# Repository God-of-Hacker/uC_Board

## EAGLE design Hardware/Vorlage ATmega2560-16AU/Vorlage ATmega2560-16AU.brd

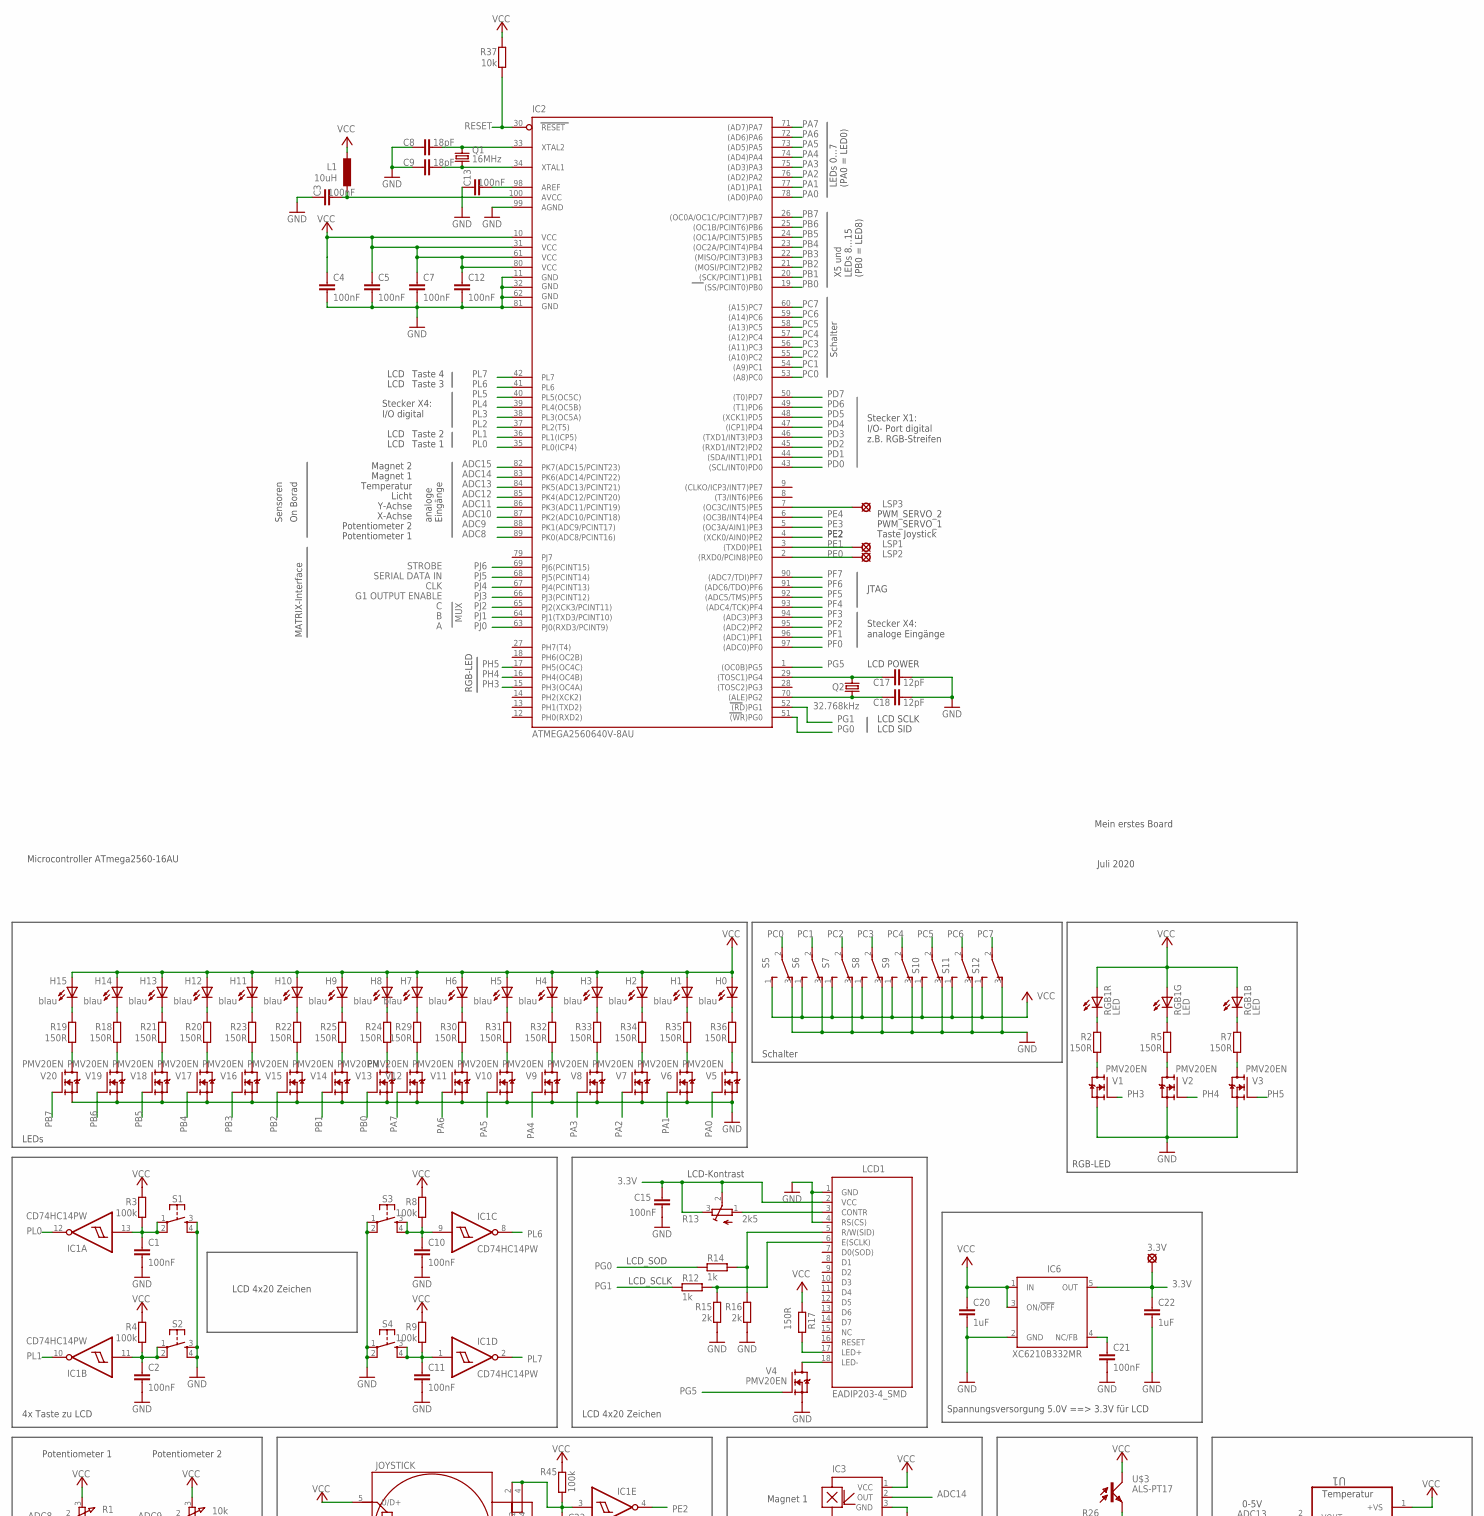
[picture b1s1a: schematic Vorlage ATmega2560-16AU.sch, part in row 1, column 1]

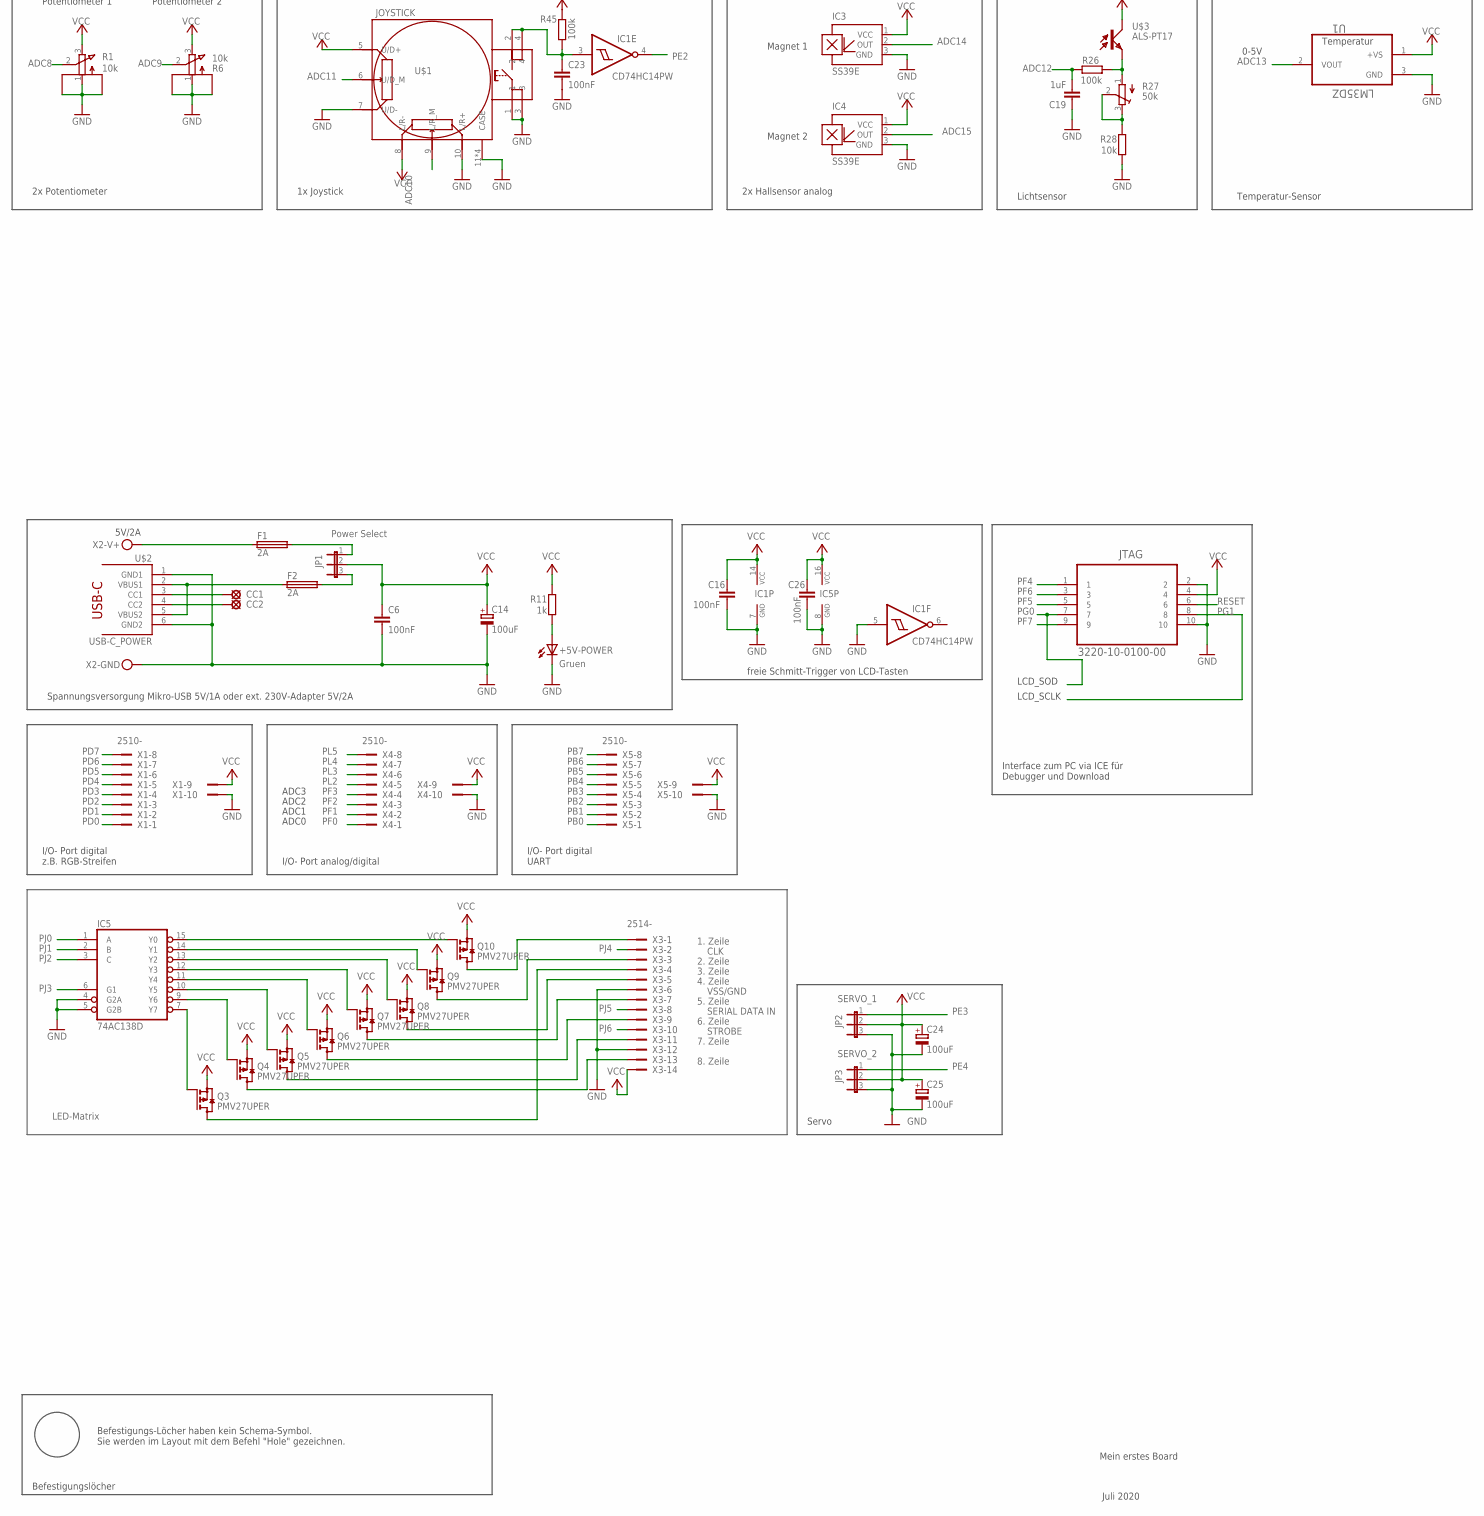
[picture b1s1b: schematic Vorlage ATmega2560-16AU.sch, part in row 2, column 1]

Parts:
3.3V: 3.3V; LSP11
+5V-POWER: Gruen; CHIPLED_1206
C1, C2, C3, C4, C5, C7, C10, C11, C12, C13, C21, C23: 100nF; C0805
C6, C15, C16, C26: 100nF; C1206
C8, C9: 18pF; C0805K
C14, C24, C25: 100uF; UD-6,3X5,8_NICHICON
C17, C18: 12pF; C0805K
C19, C20, C22: 1uF; C0805
CC1, CC2: LSP11
F1, F2: 2A; F1206
H0, H1, H2, H3, H4, H5, H6, H7, H8, H9, H10, H11, H12, H13, H14, H15: blau; CHIPLED_1206
IC1: CD74HC14PW; SO14
IC2: ATMEGA2560640V-8AU; TQFP100
IC3, IC4: SS39E; SOT23-W
IC5: 74AC138D; SO16
IC6: XC6210B332MR; SOT23-DBV
JP1: Power Select; JP2
JP2: SERVO_1; JP2
JP3: SERVO_2; JP2
JTAG: 3220-10-0100-00; SAMTEC_FTS-105-01-L-D
L1: 10uH; L2825P
LCD1: EADIP203-4_SMD; EADIP203-4SMD
LSP1, LSP2, LSP3: LSP11
Q1: 16MHz; HC49UP
Q2: 32.768kHz; TC38H
Q3, Q4, Q5, Q6, Q7, Q8, Q9, Q10: PMV27UPER; SOT23
R1, R6: 10k; EVUF
R2, R5, R7, R18, R19, R20, R21, R22, R23, R24, R25, R29, R30, R31, R32, R33, R34, R35, R36: 150R; R0805
R3, R4, R8, R9, R26, R45: 100k; R0805
R11, R12, R14: 1k; R0805
R13: 2k5; 3223G
R15, R16: 2k; R0805
R17: 150R; R1206
R27: 50k; 3223G
R28, R37: 10k; R0805
RGB1: LED; LED_MIT_DIFUSOR
S1, S2, S3, S4: TS42_4PAD
S5, S6, S7, S8, S9, S10, S11, S12: TL36POSPDT_5MM; SPDT_5MM
U1: LM35DZ; TO127P254X495-3P
U$1: JOYSTICK; RKJXV1224005
U$2: USB-C_POWER; USB-C
U$3: ALS-PT17; SOD232-W
V1, V2, V3, V4, V5, V6, V7, V8, V9, V10, V11, V12, V13, V14, V15, V16, V17, V18, V19, V20: PMV20EN; SOT23
X1, X4, X5: 2510-; PAK100/2500-10
X2: +5V; MKDSN1,5/2-5,08
X3: 2514-; PAK100/2500-14

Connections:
3.3V: 3.3V.MP, C15.1, C22.1, IC6.5 (OUT), LCD1.2 (VCC), R13.2 (S), R13.3 (E)
ADC8: IC2.89 (PK0(ADC8/PCINT16)), R1.2 (S)
ADC9: IC2.88 (PK1(ADC9/PCINT17)), R6.2 (S)
ADC10: IC2.87 (PK2(ADC10/PCINT18)), U$1.9 (L/R_M)
ADC11: IC2.86 (PK3(ADC11/PCINT19)), U$1.6 (U/D_M)
ADC12: C19.2, IC2.85 (PK4(ADC12/PCINT20)), R26.2
ADC13: IC2.84 (PK5(ADC13/PCINT21)), U1.2 (VOUT)
ADC14: IC2.83 (PK6(ADC14/PCINT22)), IC3.2 (OUT)
ADC15: IC2.82 (PK7(ADC15/PCINT23)), IC4.2 (OUT)
GND: +5V-POWER.C, C1.2, C2.2, C3.1, C4.2, C5.2, C6.2, C7.2, C8.1, C9.2, C10.2, C11.2, C12.2, C13.1, C14.-, C15.2, C16.2, C17.2, C18.2, C19.1, C20.2, C21.2, C22.2, C23.2, C24.-, C25.-, C26.2, IC1.5 (I), IC1.7 (GND), IC2.11 (GND), IC2.32 (GND1), IC2.62 (GND2), IC2.81 (GND3), IC2.99 (AGND), IC3.3 (GND), IC4.3 (GND), IC5.4 (G2A), IC5.5 (G2B), IC5.8 (GND), IC6.2 (GND), JP2.3, JP3.3, JTAG.2, JTAG.10, LCD1.1 (GND), LCD1.4 (RS(CS)), R1.1 (A), R1.M1, R1.M2, R6.1 (A), R6.M1, R6.M2, R15.1, R16.1, R28.1, S1.3, S1.4, S2.3, S2.4, S3.1, S3.2, S4.1, S4.2, S5.3 (O), S6.3 (O), S7.3 (O), S8.3 (O), S9.3 (O), S10.3 (O), S11.3 (O), S12.3 (O), U1.3 (GND), U$1.1, U$1.3, U$1.7 (U/D-), U$1.10 (L/R+), U$1.11 (CASE), U$1.12 (CASE), U$1.15 (CASE), U$1.16 (CASE), U$2.1 (GND1), U$2.6 (GND2), V1.2 (S), V2.2 (S), V3.2 (S), V4.2 (S), V5.2 (S), V6.2 (S), V7.2 (S), V8.2 (S), V9.2 (S), V10.2 (S), V11.2 (S), V12.2 (S), V13.2 (S), V14.2 (S), V15.2 (S), V16.2 (S), V17.2 (S), V18.2 (S), V19.2 (S), V20.2 (S), X1.10, X2.1.1, X2.1.2, X3.6, X3.12, X4.10, X5.10
H1: H15.C, R19.2
H7: H7.C, R29.2
unnamed: R7.2, RGB1.1 (C)
unnamed: R5.2, RGB1.2 (C)
unnamed: F1.2, JP1.1
unnamed: F2.2, JP1.3
unnamed: R36.1, V5.3 (D)
unnamed: R35.1, V6.3 (D)
unnamed: R34.1, V7.3 (D)
unnamed: CC1.MP, U$2.3 (CC1)
unnamed: C23.1, IC1.3 (I), R45.2, U$1.2, U$1.4
unnamed: CC2.MP, U$2.4 (CC2)
unnamed: R2.2, RGB1.3 (C)
unnamed: LCD1.18 (LED-), V4.3 (D)
unnamed: R33.1, V8.3 (D)
unnamed: R32.1, V9.3 (D)
unnamed: R31.1, V10.3 (D)
unnamed: R30.1, V11.3 (D)
unnamed: R29.1, V12.3 (D)
unnamed: IC2.7 ((OC3C/INT5)PE5), LSP3.MP
unnamed: R26.1, R27.1 (A), U$3.E
unnamed: R27.2 (S), R27.3 (E), R28.2
unnamed: C1.1, IC1.13 (I), R3.2, S1.1, S1.2
unnamed: C2.1, IC1.11 (I), R4.2, S2.1, S2.2
unnamed: C11.1, IC1.1 (I), R9.2, S4.3, S4.4
unnamed: C10.1, IC1.9 (I), R8.2, S3.3, S3.4
unnamed: C9.1, IC2.34 (XTAL1), Q1.1
unnamed: C3.2, IC2.100 (AVCC), L1.2
unnamed: R2.1, V1.3 (D)
unnamed: R5.1, V2.3 (D)
unnamed: R7.1, V3.3 (D)
unnamed: C13.2, IC2.98 (AREF)
unnamed: F2.1, U$2.2 (VBUS1), U$2.5 (VBUS2)
unnamed: C17.1, IC2.29 ((TOSC1)PG4), Q2.1
unnamed: H6.C, R30.2
unnamed: LCD1.3 (CONTR), R13.1 (A)
unnamed: C18.1, IC2.70 ((ALE)PG2), Q2.2
unnamed: C8.2, IC2.33 (XTAL2), Q1.2
unnamed: LCD1.6 (E(SCLK)), R12.1, R15.2
unnamed: LCD1.5 (R/W(SID)), R14.1, R16.2
unnamed: H14.C, R18.2
unnamed: H12.C, R20.2
unnamed: H2.C, R34.2
unnamed: H4.C, R32.2
unnamed: H5.C, R31.2
unnamed: H13.C, R21.2
unnamed: H10.C, R22.2
unnamed: H3.C, R33.2
unnamed: H11.C, R23.2
unnamed: H8.C, R24.2
unnamed: H0.C, R36.2
unnamed: H1.C, R35.2
unnamed: H9.C, R25.2
unnamed: +5V-POWER.A, R11.2
unnamed: R24.1, V13.3 (D)
unnamed: R25.1, V14.3 (D)
unnamed: R22.1, V15.3 (D)
unnamed: R23.1, V16.3 (D)
unnamed: R20.1, V17.3 (D)
unnamed: R21.1, V18.3 (D)
unnamed: R18.1, V19.3 (D)
unnamed: R19.1, V20.3 (D)
unnamed: C21.1, IC6.4 (NC/FB)
unnamed: F1.1, X2.2.1, X2.2.2
unnamed: LCD1.17 (LED+), R17.1
unnamed: IC5.15 (Y0), Q10.1 (G)
unnamed: Q10.3 (D), X3.1
unnamed: IC5.14 (Y1), Q9.1 (G)
unnamed: IC5.13 (Y2), Q8.1 (G)
unnamed: IC5.12 (Y3), Q7.1 (G)
unnamed: IC5.11 (Y4), Q6.1 (G)
unnamed: IC5.10 (Y5), Q5.1 (G)
unnamed: IC5.9 (Y6), Q4.1 (G)
unnamed: IC5.7 (Y7), Q3.1 (G)
unnamed: Q9.3 (D), X3.3
unnamed: Q3.3 (D), X3.4
unnamed: Q8.3 (D), X3.5
unnamed: Q7.3 (D), X3.7
unnamed: Q6.3 (D), X3.9
unnamed: Q5.3 (D), X3.11
unnamed: Q4.3 (D), X3.13
PA0: IC2.78 ((AD0)PA0), V5.1 (G)
PA1: IC2.77 ((AD1)PA1), V6.1 (G)
PA2: IC2.76 ((AD2)PA2), V7.1 (G)
PA3: IC2.75 ((AD3)PA3), V8.1 (G)
PA4: IC2.74 ((AD4)PA4), V9.1 (G)
PA5: IC2.73 ((AD5)PA5), V10.1 (G)
PA6: IC2.72 ((AD6)PA6), V11.1 (G)
PA7: IC2.71 ((AD7)PA7), V12.1 (G)
PB0: IC2.19 ((SS/PCINT0)PB0), V13.1 (G), X5.1
PB1: IC2.20 ((SCK/PCINT1)PB1), V14.1 (G), X5.2
PB2: IC2.21 ((MOSI/PCINT2)PB2), V15.1 (G), X5.3
PB3: IC2.22 ((MISO/PCINT3)PB3), V16.1 (G), X5.4
PB4: IC2.23 ((OC2A/PCINT4)PB4), V17.1 (G), X5.5
PB5: IC2.24 ((OC1A/PCINT5)PB5), V18.1 (G), X5.6
PB6: IC2.25 ((OC1B/PCINT6)PB6), V19.1 (G), X5.7
PB7: IC2.26 ((OC0A/OC1C/PCINT7)PB7), V20.1 (G), X5.8
PC0: IC2.53 ((A8)PC0), S5.2
PC1: IC2.54 ((A9)PC1), S6.2
PC2: IC2.55 ((A10)PC2), S7.2
PC3: IC2.56 ((A11)PC3), S8.2
PC4: IC2.57 ((A12)PC4), S9.2
PC5: IC2.58 ((A13)PC5), S10.2
PC6: IC2.59 ((A14)PC6), S11.2
PC7: IC2.60 ((A15)PC7), S12.2
PD0: IC2.43 ((SCL/INT0)PD0), X1.1
PD1: IC2.44 ((SDA/INT1)PD1), X1.2
PD2: IC2.45 ((RXD1/INT2)PD2), X1.3
PD3: IC2.46 ((TXD1/INT3)PD3), X1.4
PD4: IC2.47 ((ICP1)PD4), X1.5
PD5: IC2.48 ((XCK1)PD5), X1.6
PD6: IC2.49 ((T1)PD6), X1.7
PD7: IC2.50 ((T0)PD7), X1.8
PE0: IC2.2 ((RXD0/PCIN8)PE0), LSP2.MP
PE1: IC2.3 ((TXD0)PE1), LSP1.MP
PE2: IC1.4 (O), IC2.4 ((XCK0/AIN0)PE2)
PE3: IC2.5 ((OC3A/AIN1)PE3), JP2.1
PE4: IC2.6 ((OC3B/INT4)PE4), JP3.1
PF0: IC2.97 ((ADC0)PF0), X4.1
PF1: IC2.96 ((ADC1)PF1), X4.2
PF2: IC2.95 ((ADC2)PF2), X4.3
PF3: IC2.94 ((ADC3)PF3), X4.4
PF4: IC2.93 ((ADC4/TCK)PF4), JTAG.1
PF5: IC2.92 ((ADC5/TMS)PF5), JTAG.5
PF6: IC2.91 ((ADC6/TDO)PF6), JTAG.3
PF7: IC2.90 ((ADC7/TDI)PF7), JTAG.9
PG0: IC2.51 ((WR)PG0), JTAG.7, R14.2
PG1: IC2.52 ((RD)PG1), JTAG.8, R12.2
PG5: IC2.1 ((OC0B)PG5), V4.1 (G)
PH3: IC2.15 (PH3(OC4A)), V1.1 (G)
PH4: IC2.16 (PH4(OC4B)), V2.1 (G)
PH5: IC2.17 (PH5(OC4C)), V3.1 (G)
PJ0: IC2.63 (PJ0(RXD3/PCINT9)), IC5.1 (A)
PJ1: IC2.64 (PJ1(TXD3/PCINT10)), IC5.2 (B)
PJ2: IC2.65 (PJ2(XCK3/PCINT11)), IC5.3 (C)
PJ3: IC2.66 (PJ3(PCINT12)), IC5.6 (G1)
PJ4: IC2.67 (PJ4(PCINT13)), X3.2
PJ5: IC2.68 (PJ5(PCINT14)), X3.8
PJ6: IC2.69 (PJ6(PCINT15)), X3.10
PL0: IC1.12 (O), IC2.35 (PL0(ICP4))
PL1: IC1.10 (O), IC2.36 (PL1(ICP5))
PL2: IC2.37 (PL2(T5)), X4.5
PL3: IC2.38 (PL3(OC5A)), X4.6
PL4: IC2.39 (PL4(OC5B)), X4.7
PL5: IC2.40 (PL5(OC5C)), X4.8
PL6: IC1.8 (O), IC2.41 (PL6)
PL7: IC1.2 (O), IC2.42 (PL7)
RESET: IC2.30 (RESET), JTAG.6, R37.1
VCC: C4.1, C5.1, C6.1, C7.1, C12.1, C14.+, C16.1, C20.1, C24.+, C25.+, C26.1, H0.A, H1.A, H2.A, H3.A, H4.A, H5.A, H6.A, H7.A, H8.A, H9.A, H10.A, H11.A, H12.A, H13.A, H14.A, H15.A, IC1.14 (VCC), IC2.10 (VCC), IC2.31 (VCC1), IC2.61 (VCC2), IC2.80 (VCC3), IC3.1 (VCC), IC4.1 (VCC), IC5.16 (VCC), IC6.1 (IN), IC6.3 (ON/!OFF), JP1.2, JP2.2, JP3.2, JTAG.4, L1.1, Q3.2 (S), Q4.2 (S), Q5.2 (S), Q6.2 (S), Q7.2 (S), Q8.2 (S), Q9.2 (S), Q10.2 (S), R1.3 (E), R3.1, R4.1, R6.3 (E), R8.1, R9.1, R11.1, R17.2, R37.2, R45.1, RGB1.4 (A), RGB1.5 (A), RGB1.6 (A), S5.1 (S), S6.1 (S), S7.1 (S), S8.1 (S), S9.1 (S), S10.1 (S), S11.1 (S), S12.1 (S), U1.1 (+VS), U$1.5 (U/D+), U$1.8 (L/R-), U$3.C, X1.9, X3.14, X4.9, X5.9

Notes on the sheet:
Microcontroller ATmega2560-16AU
LCD SID
LCD SCLK
Taste 1
Taste 2
Taste 3
Taste 4
LCD
LCD POWER
Mein erstes Board
Juli 2020
JTAG
analoge Eingänge
G1 OUTPUT ENABLE
MUX
CLK
SERIAL DATA IN
STROBE
Magnet 2
Magnet 1
Temperatur
Licht
Y-Achse
X-Achse
Potentiometer 2
Potentiometer 1
Stecker X1: I/O- Port digital z.B. RGB-Streifen
MATRIX-Interface
Sensoren
On Borad
Stecker X4: analoge Eingänge
Stecker X4: I/O digital
Taste Joystick
PWM_SERVO_1
PWM_SERVO_2
I/O- Port digital UART
LCD 4x20 Zeichen
Spannungsversorgung Mikro-USB 5V/1A oder ext. 230V-Adapter 5V/2A
Spannungsversorgung 5.0V ==> 3.3V für LCD
Interface zum PC via ICE für Debugger und Download

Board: 2 copper layers, 152 parts (0 on the bottom side), 159 nets, no tracks yet.

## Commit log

2021-11-11 Bauteile auf 0805
